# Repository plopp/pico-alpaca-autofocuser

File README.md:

# pico-alpaca-autofocuser

An ASCOM Alpaca focuser (IFocuserV4, absolute) for a Raspberry Pi Pico 2 W, written in
MicroPython, for autofocus with NINA. It drives a TMC2209 stepper driver over Wi-Fi.
It passes ASCOM ConformU 4.1 against the desktop simulator (`sim.py`); the run on real
hardware is pending a separate motor supply (see Wiring).

## Hardware

There's a carrier PCB in [`hardware/`](hardware/README.md): 80 × 50 mm, assembled by JLCPCB,
with sockets for the Pico 2 W and the TMC2209, a 12 V barrel jack, a motor connector and a
3.5 mm jack for a DS18B20 temperature sensor. A printable case for the board and the motor is
in [`case/`](case/README.md). The table below is for breadboard builds.

## Wiring (breadboard)

| TMC2209 (BigTreeTech v1.3) | Connect to |
|---|---|
| STEP | Pico GP16 (pin 21) |
| DIR | Pico GP20 (pin 26) |
| EN | Pico GP21 (pin 27) |
| VIO | Pico 3V3 OUT (pin 36) |
| GND (both) | Pico GND and the motor supply's GND |
| VM | Motor supply, 12 V recommended, with ~100 µF across VM/GND |
| A1/A2, B1/B2 | One motor coil each |
| MS1, MS2 | Unconnected (1/8 microstepping) |

Don't power VM from the Pico's USB 5 V (VBUS): the motor can hang or reset the board.

## Setup

1. Install MicroPython 1.27+ for the Pico 2 W.
2. Create `pico/secret.toml` (never committed):
   ```toml
   [wifi]
   ssid = "your-network-name"
   password = "your-wifi-password"
   ```
3. Adjust `pico/config.toml` if needed (range, speed, direction).
4. `python3 -m venv .venv && .venv/bin/pip install mpremote`, then `tools/deploy.sh`.

At power-up the LED blinks while joining Wi-Fi and stays on when connected. In NINA,
choose the focuser from the Alpaca devices list. Discovery only works when NINA's PC is on
the same subnet as the Pico; otherwise add it manually by IP address, port 5555.

**Position:** the focuser has no encoder. Every power-up it reports the middle of the
range (50000 of 0–100000 by default), so set focus roughly by hand before powering on.

## Control page

Open `http://<pico-ip>:5555/setup` in a browser (phone or laptop). You can:
- see the live position and temperature
- jog ±10 / 100 / 1000 steps, move to a position, or halt
- reset the position to the start value (50000) without moving
- change the basic settings: name, range, start position, speed, direction, hold when idle

Speed, direction and hold take effect at once; the others after **Restart**. Wi-Fi, port and
pins can only be changed in the files on the Pico. Without NINA connected, a manual move powers
the motor only for the move. While NINA is connected the page warns you that moves will disturb
autofocus.

## Temperature (DS18B20) and refocusing

The focuser reports `Temperature` to NINA from a DS18B20 on GP22 (the 3.5 mm jack on the
carrier board). In NINA's Advanced Sequencer, add the trigger **"Autofocus after temperature
change"**, for example 1 °C. The focuser only measures; NINA decides when to refocus.

A **Shelly DS18B20** probe works directly. Fit a 3-pole (TRS) 3.5 mm plug:

| Shelly wire | 3.5 mm plug |
|---|---|
| yellow (data) | tip |
| red (VCC) | ring (3.3 V from the board) |
| black (GND) | sleeve |

Check the colours against the label or documentation of your probe before plugging in. On a
breadboard, add a 4.7 kΩ resistor from data to 3.3 V.

With no sensor plugged in, `Temperature` reports "not implemented" and NINA's trigger simply
won't fire. A sensor plugged in later is found within 30 s.

## Development

```bash
python3 -m pytest tests -q   # tests on the PC with simulated hardware
python3 sim.py               # run the server on the PC with a simulated motor
```

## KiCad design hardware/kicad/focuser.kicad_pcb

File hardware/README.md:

# Focuser carrier PCB

An 80 × 50 mm, 2-layer carrier board for the Pico 2 W focuser. JLCPCB makes and assembles
it; you plug in your own **Raspberry Pi Pico 2 W** and **BigTreeTech TMC2209 v1.3**.
A single 12 V supply powers the motor and the Pico.

## Ordering at JLCPCB

Everything to upload is in `fab/`:

1. **PCB:** upload `focuser-gerbers.zip`. Keep the defaults: 2 layers, 1.6 mm, any colour.
2. **Assembly:** turn on *PCB Assembly*, **top side**. The sockets, barrel jack, motor
   connector and U1 are through-hole, so make sure through-hole assembly is included.
3. Upload **`focuser-bom-jlc.csv`** (BOM) and **`focuser-cpl-jlc.csv`** (pick and place).
4. **U1 (RECOM R-78E5.0-0.5)** is JLCPCB part **C18212367** (Extended). If it is ever out of
   stock, any 7805-pinout 5 V switching module with at least 15 V input and at least 0.5 A
   fits the same holes (pin 1 = VIN in the square pad): RECOM R-78E5.0-1.0, Mornsun or DEXU
   K7805-500R3 (LCSC C909662), Traco TSR 1-2450.
5. **Check the placement preview before paying.** JLCPCB's parts don't always share KiCad's
   zero rotation. Look especially at:
   - the **polarity** of D1/D2 (stripe = cathode) and C1 (+)
   - that **J1** and **J3** face outwards at the board edges

   Fix rotations in the preview if needed.
6. Solder jumpers JP1/JP2 are pads only; nothing is placed on them.
7. **J1 and J3 stick out 2 mm past the rear (left, short) edge** on purpose. If JLCPCB adds
   assembly edge rails, they must go on the long edges, not the rear edge. Say so in the
   order remarks: "J1 and J3 overhang the left short edge by 2 mm; no edge rail on that side."

## Using the board

| Connector | Pinout |
|---|---|
| **J1** 12 V barrel jack | 5.5 × 2.1 mm plug, **centre positive**, 12 V. The jack (XUNPU DC-005-A200) is rated 0.5 A, which is enough for a focuser at modest motor current. |
| **J2** motor (JST XH 4-pin) | 1 = A1, 2 = A2, 3 = B1, 4 = B2. **A1/A2 must be one coil, B1/B2 the other.** Check with a multimeter: a few ohms within a coil, open circuit between coils. |
| **J3** 3.5 mm jack, DS18B20 (rear edge, below the 12 V jack) | Tip = data (GP22, 4.7 kΩ pull-up on the board), Ring = 3.3 V (through 100 Ω), Sleeve = GND. Use a 3-pole (TRS) plug. |
| USB | The Pico's own USB port, next to J1, for flashing. USB and 12 V can be connected at the same time. |

**Plugging in the modules**
- **Pico 2 W:** USB end towards the J1 edge (silkscreen "USB"), components facing up.
- **TMC2209:** components (heatsink) up, with its **EN** pin in the hole marked **EN** and its
  **VM** pin in the hole marked **VM**. Both are at the end nearest the motor connector; the
  logic row (EN…DIR) is on the board-edge side. Plugging it in any other way puts 12 V on the
  wrong pins and destroys the driver, so check before applying power.
- Set the motor current with the TMC2209's potentiometer *before* connecting the motor. A
  focuser needs little torque: start low.

**Microstepping:** JP1/JP2 open (default) = 1/8 step, which is what the firmware assumes.
Bridging a jumper ties MS1 (JP1) or MS2 (JP2) to 3.3 V (BTT TMC2209 v1.3 table):

| JP1 (MS1) | JP2 (MS2) | Microsteps | Steps per motor turn |
|---|---|---|---|
| open | open | 8 (default) | 1600 |
| bridged | open | 2 | 400 |
| open | bridged | 4 | 800 |
| bridged | bridged | 16 | 3200 |

After changing it, scale `max_step`, `start_position` and `steps_per_sec` to match (on the
control page, or in `config.toml`).

**Wi-Fi:** the Pico's antenna end (opposite USB) has no copper under it (datasheet keep-out,
14 × 9 mm) and the driver sits more than 10 mm away. Don't put metal near that end in the case.

**Mounting:** no screw holes. The board slides into slots in the case, and the 2.5 mm strips along both
long edges are kept free of parts.
The rear wall is meant to be 2 mm thick: J1's body (2 mm past the edge) and J3's nose (2 mm,
5 mm diameter) reach through it and end flush with its outside face.

## Pins used on the Pico

STEP GP16 · DIR GP20 · EN GP21 (pulled high = driver off until the Pico boots) · DS18B20 GP22 ·
3V3 OUT → driver VIO · VSYS ← 5 V from U1 (through a Schottky diode).

## Rebuilding the design

All of it is generated from [`design.py`](design.py):

```bash
hardware/setup_tools.sh          # once: KiCad 10.0.7 + FreeRouting under ~/.local/opt
hardware/build.sh                # schematic -> placement -> autorouting -> fab/
python3 -m pytest tests/hardware -q
```

`kicad/focuser.kicad_pro` opens in KiCad 10 for viewing or hand edits. Running the build again
overwrites hand edits.

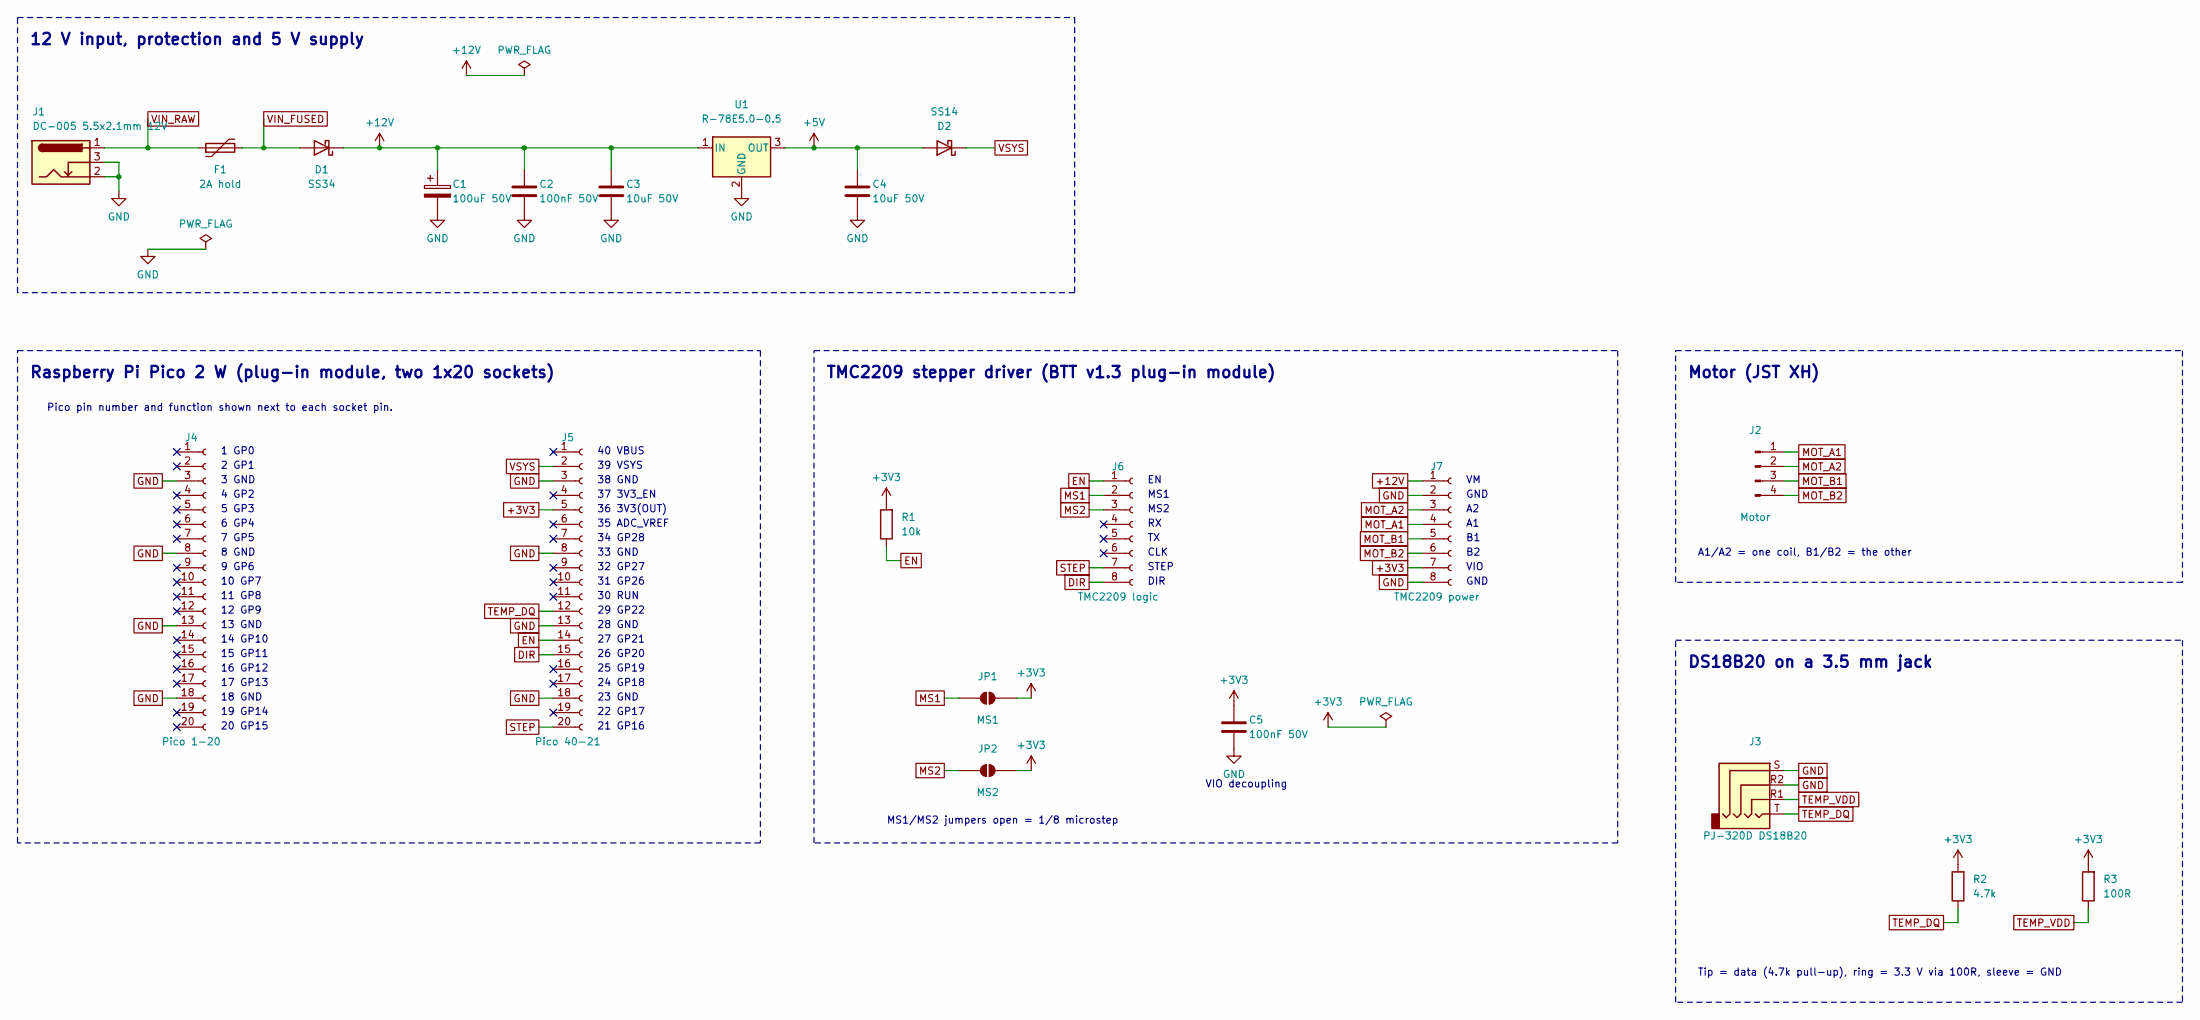
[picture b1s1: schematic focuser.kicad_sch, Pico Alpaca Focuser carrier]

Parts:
C1: 100uF 50V; CP_Elec_8x10.5; LCSC C72480
C2, C5: 100nF 50V; C_0805_2012Metric; LCSC C49678
C3, C4: 10uF 50V; C_1206_3216Metric; LCSC C89632
D1: SS34; D_SMA; LCSC C8678
D2: SS14; D_SMA; LCSC C2480
F1: 2A hold; Fuse_1812_4532Metric; LCSC C2982282
J1: DC-005 5.5x2.1mm 12V; BarrelJack_XunPu_DC-005-A200; LCSC C720557
J2: Motor; JST_XH_B4B-XH-A_1x04_P2.50mm_Vertical; LCSC C144395
J3: PJ-320D DS18B20; Jack_3.5mm_KoreanHropartsElec_PJ-320D-4A_Horizontal; LCSC C95562
J4: Pico 1-20; PinSocket_1x20_P2.54mm_Vertical; LCSC C2905423
J5: Pico 40-21; PinSocket_1x20_P2.54mm_Vertical; LCSC C2905423
J6: TMC2209 logic; PinSocket_1x08_P2.54mm_Vertical; LCSC C2905417
J7: TMC2209 power; PinSocket_1x08_P2.54mm_Vertical; LCSC C2905417
JP1: MS1; SolderJumper-2_P1.3mm_Open_Pad1.0x1.5mm
JP2: MS2; SolderJumper-2_P1.3mm_Open_Pad1.0x1.5mm
R1: 10k; R_0603_1608Metric; LCSC C25804
R2: 4.7k; R_0603_1608Metric; LCSC C23162
R3: 100R; R_0603_1608Metric; LCSC C22775
U1: R-78E5.0-0.5; Converter_DCDC_RECOM_R-78E-0.5_THT; LCSC C18212367

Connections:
+3V3: C5.1, J5.5, J7.7, JP1.2 (B), JP2.2 (B), R1.2, R2.2, R3.2
+5V: C4.1, D2.2 (A), U1.3 (OUT)
+12V: C1.1, C2.1, C3.1, D1.1 (K), J7.1, U1.1 (IN)
DIR: J5.15, J6.8
EN: J5.14, J6.1, R1.1
GND: C1.2, C2.2, C3.2, C4.2, C5.2, J1.2, J1.3, J3.R2, J3.S, J4.3, J4.8, J4.13, J4.18, J5.3, J5.8, J5.13, J5.18, J7.2, J7.8, U1.2 (GND)
MOT_A1: J2.1, J7.4
MOT_A2: J2.2, J7.3
MOT_B1: J2.3, J7.5
MOT_B2: J2.4, J7.6
MS1: J6.2, JP1.1 (A)
MS2: J6.3, JP2.1 (A)
STEP: J5.20, J6.7
TEMP_DQ: J3.T, J5.12, R2.1
TEMP_VDD: J3.R1, R3.1
VIN_FUSED: D1.2 (A), F1.2
VIN_RAW: F1.1, J1.1
VSYS: D2.1 (K), J5.2

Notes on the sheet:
12 V input, protection and 5 V supply
Raspberry Pi Pico 2 W (plug-in module, two 1x20 sockets)
Pico pin number and function shown next to each socket pin.
1 GP0
2 GP1
3 GND
4 GP2
5 GP3
6 GP4
7 GP5
8 GND
9 GP6
10 GP7
11 GP8
12 GP9
13 GND
14 GP10
15 GP11
16 GP12
17 GP13
18 GND
19 GP14
20 GP15
40 VBUS
39 VSYS
38 GND
37 3V3_EN
36 3V3(OUT)
35 ADC_VREF
34 GP28
33 GND
32 GP27
31 GP26
30 RUN
29 GP22
28 GND
27 GP21
26 GP20
25 GP19
24 GP18

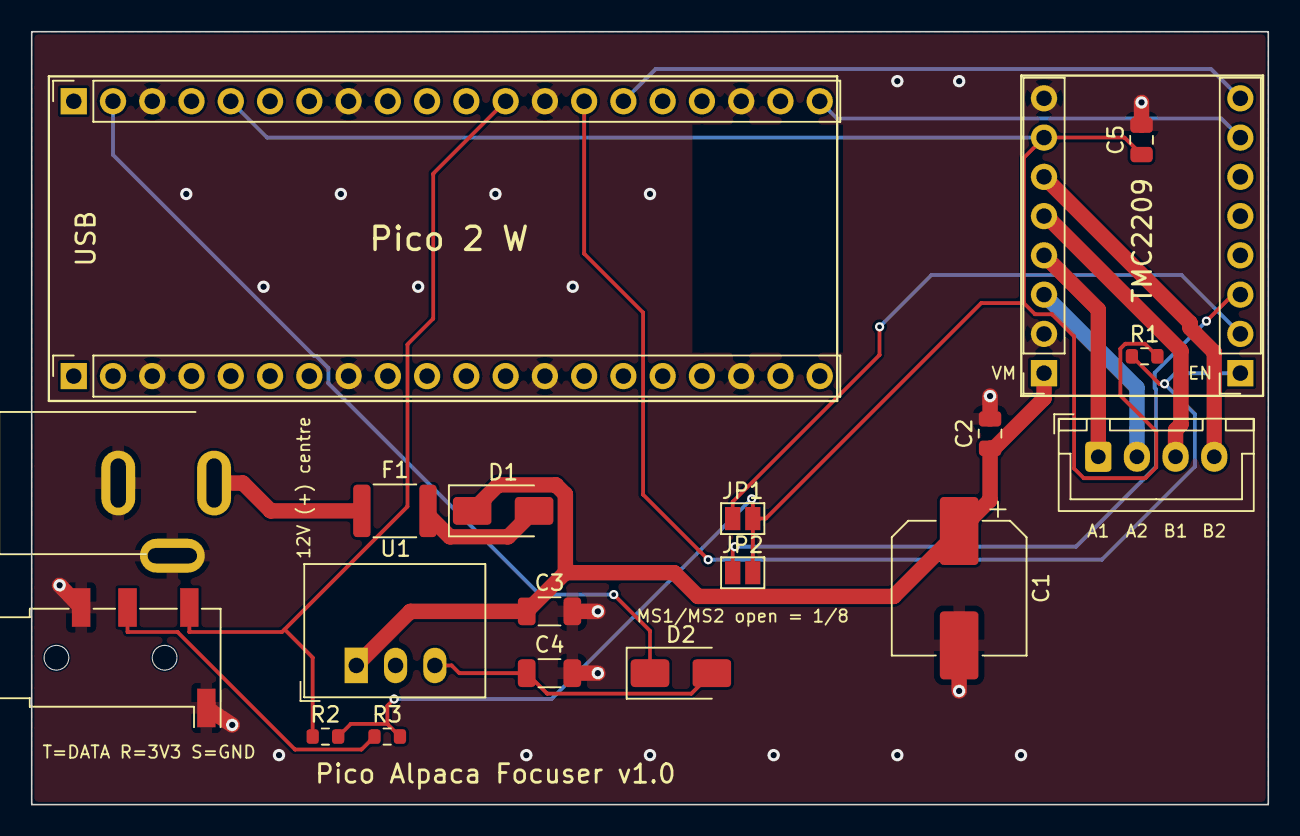
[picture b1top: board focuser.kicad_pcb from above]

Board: 2 copper layers, 80.0 x 50.0 mm, 21 parts (0 on the bottom side), 18 nets.

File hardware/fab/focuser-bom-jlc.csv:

Comment,Designator,Footprint,LCSC Part #,Manufacturer Part
100uF 50V,C1,CP_Elec_8x10.5,C72480,
100nF 50V,"C2,C5",C_0805_2012Metric,C49678,
10uF 50V,"C3,C4",C_1206_3216Metric,C89632,
SS34,D1,D_SMA,C8678,
SS14,D2,D_SMA,C2480,
2A hold,F1,Fuse_1812_4532Metric,C2982282,
DC-005 5.5x2.1mm 12V,J1,BarrelJack_XunPu_DC-005-A200,C720557,
Motor,J2,JST_XH_B4B-XH-A_1x04_P2.50mm_Vertical,C144395,
PJ-320D DS18B20,J3,Jack_3.5mm_KoreanHropartsElec_PJ-320D-4A_Horizontal,C95562,
Pico 1-20,J4,PinSocket_1x20_P2.54mm_Vertical,C2905423,
Pico 40-21,J5,PinSocket_1x20_P2.54mm_Vertical,C2905423,
TMC2209 logic,J6,PinSocket_1x08_P2.54mm_Vertical,C2905417,
TMC2209 power,J7,PinSocket_1x08_P2.54mm_Vertical,C2905417,
10k,R1,R_0603_1608Metric,C25804,
4.7k,R2,R_0603_1608Metric,C23162,
100R,R3,R_0603_1608Metric,C22775,
R-78E5.0-0.5,U1,Converter_DCDC_RECOM_R-78E-0.5_THT,C18212367,R-78E5.0-0.5

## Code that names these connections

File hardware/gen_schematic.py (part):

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    tick = 43.18
    s.wire(j1p1, (tick, rail), s.tap('F1', '1'))
    s.wire((tick, rail), (tick, rail - 2 * G))
    s.label('VIN_RAW', tick, rail - 2 * G, RIGHT)
    tick = 63.5
    s.wire(s.tap('F1', '2'), (tick, rail), s.tap('D1', '2'))
    s.wire((tick, rail), (tick, rail - 2 * G))
    s.label('VIN_FUSED', tick, rail - 2 * G, RIGHT)
    # +12 V rail with its capacitors, the driver's VM and the 5 V regulator
    node = 83.82
    s.wire(s.tap('D1', '1'), (node, rail))
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    s.wire((167.64, rail), s.tap('D2', '2'))
    k = s.tap('D2', '1')
    s.wire(k, (k[0] + 2 * G, rail))
    s.label('VSYS', k[0] + 2 * G, rail, RIGHT)


def pico_block(s):
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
